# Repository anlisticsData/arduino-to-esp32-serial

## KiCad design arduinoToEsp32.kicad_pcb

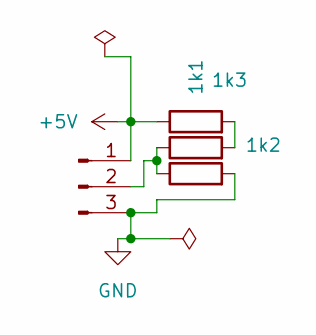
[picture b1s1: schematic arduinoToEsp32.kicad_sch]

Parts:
1k1, 1k2, 1k3: R; R_Axial_DIN0309_L9.0mm_D3.2mm_P15.24mm_Horizontal
J1: Conn_01x03_Pin; SolderWire-0.75sqmm_1x03_P4.8mm_D1.25mm_OD2.3mm

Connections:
+5V: 1k1.1, J1.1
GND: 1k3.2, J1.3
unnamed: 1k1.2, 1k2.2
unnamed: 1k2.1, 1k3.1, J1.2

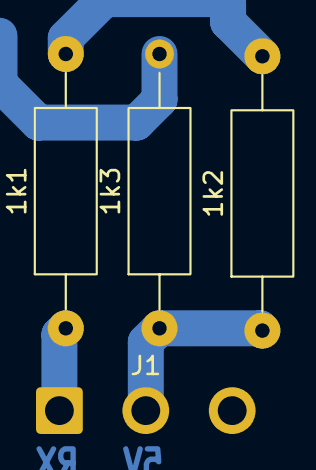
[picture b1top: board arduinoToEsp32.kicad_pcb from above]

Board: 2 copper layers, 4 parts (0 on the bottom side), 4 nets.

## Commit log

2026-02-16 desenho iniciado
2026-02-16 adicionado os componentes
2026-02-16 adicionado os componentes ligações
2026-02-16 esquematico instalado
2026-02-16 correção do esquematico
2026-02-16 trilhas adicionadas
2026-02-16 finalizado
2026-02-16 trilhas modificado e nomes retirados
